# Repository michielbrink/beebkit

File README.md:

# beepkit
An IR to sound converter

You will need the following libraries for the sourcecode:
* https://github.com/PaulStoffregen/TimerOne (newest from Github)
* IR Remote (From the library installer)

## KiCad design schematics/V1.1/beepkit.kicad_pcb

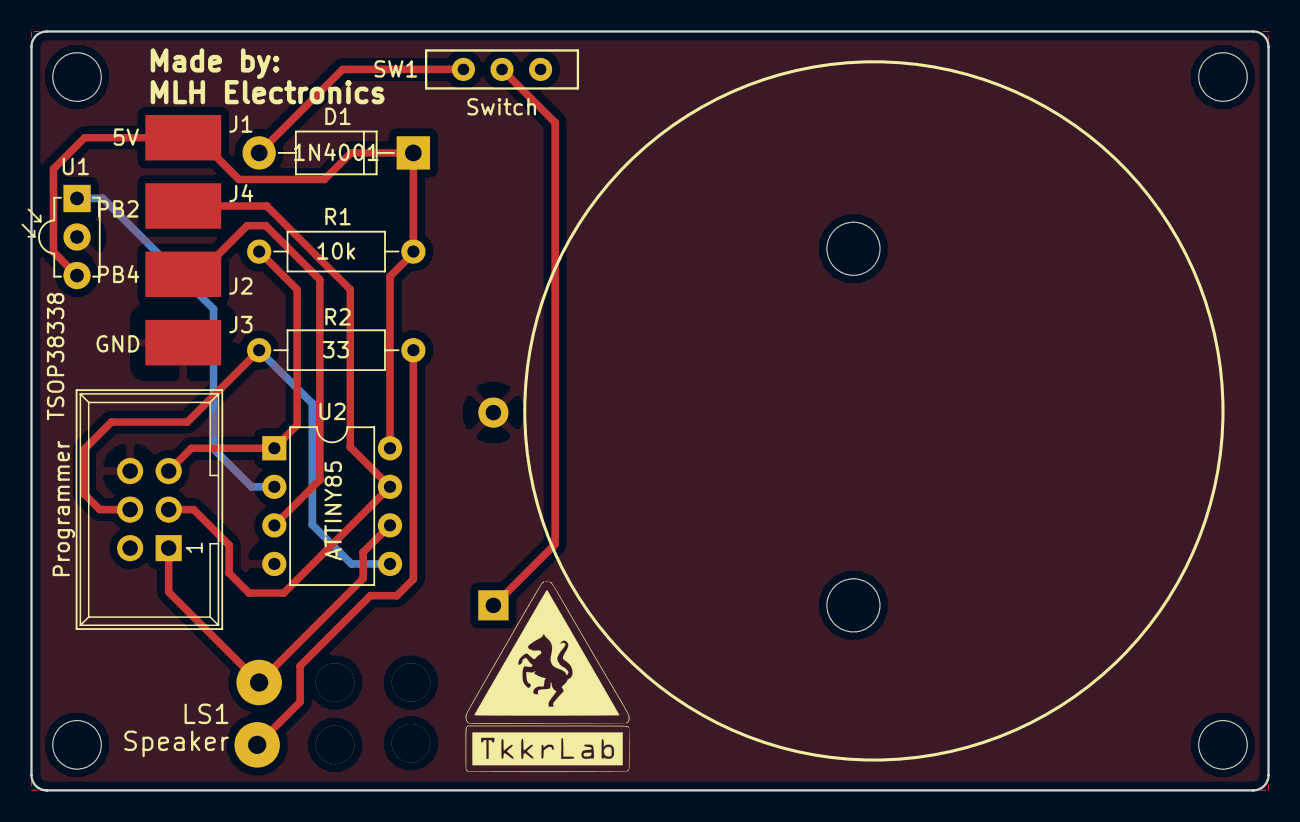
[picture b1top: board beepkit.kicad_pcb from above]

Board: 2 copper layers, 81.5 x 50.0 mm, 17 parts (1 on the bottom side), 11 nets.

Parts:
BT1: Battery; Keystone_2479_3xAAA
CON1: Programmer; IDC_Header_Straight_6pins
D1: 1N4001; D_DO-41_SOD81_P10.16mm_Horizontal
J1: 5V; SolderWirePad_single_SMD_5x10mm
J2: PB4; SolderWirePad_single_SMD_5x10mm
J3: GND; SolderWirePad_single_SMD_5x10mm
J4: PB2; SolderWirePad_single_SMD_5x10mm
LS1: Speaker; 2p_wire_terminal
MK1, MK2, MK3, MK4: Mounting_Hole; MountingHole_3.2mm_M3_ISO7380
R1: 10k; R_Axial_DIN0207_L6.3mm_D2.5mm_P10.16mm_Horizontal
R2: 33; R_Axial_DIN0207_L6.3mm_D2.5mm_P10.16mm_Horizontal
SW1: Switch; EOZ-1K2-SPDT-CO
U1: TSOP38338; IRReceiver_Vishay_MINICAST-3pin
U2: ATTINY85; DIP-8_W7.62mm

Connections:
/MISO: CON1.1, LS1.1, U2.6
/MOSI: CON1.4, R2.2, U2.5
/SCK: CON1.3, J4.1, U2.7
/~RST~: CON1.5, R1.1, U2.1
GND: BT1.2, CON1.6, J3.1, U1.2, U2.4
unnamed: BT1.1, SW1.2
unnamed: D1.1, J1.1, R1.2, U1.3, U2.8
unnamed: D1.2, SW1.3
unnamed: J2.1, U2.3
unnamed: LS1.2, R2.1
unnamed: U1.1, U2.2

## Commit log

2017-09-24 add source
2017-09-24 add pdf
